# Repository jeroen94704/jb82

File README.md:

# JB82: A compact, 82-key mechanical keyboard

I'm a bit of a keyboard nerd, and my life's problem was that I couldn't find a keyboard that perfectly fit my preferences:

* Reasonably compact
* Full row of dedicated F-keys
* A complete set of nav-keys (home/end, ins/del, pgup/pgdn)
* Not have all the keys crammed together, so I can feel my way to the nav-keys

The layout in this repo has all that. Here you will find the kicad project for the PCB design and some supporting files for the 3D-printable case (which can be found here: https://www.printables.com/model/626812-jb82-keyboard-enclosure) and the keyboard firmware.

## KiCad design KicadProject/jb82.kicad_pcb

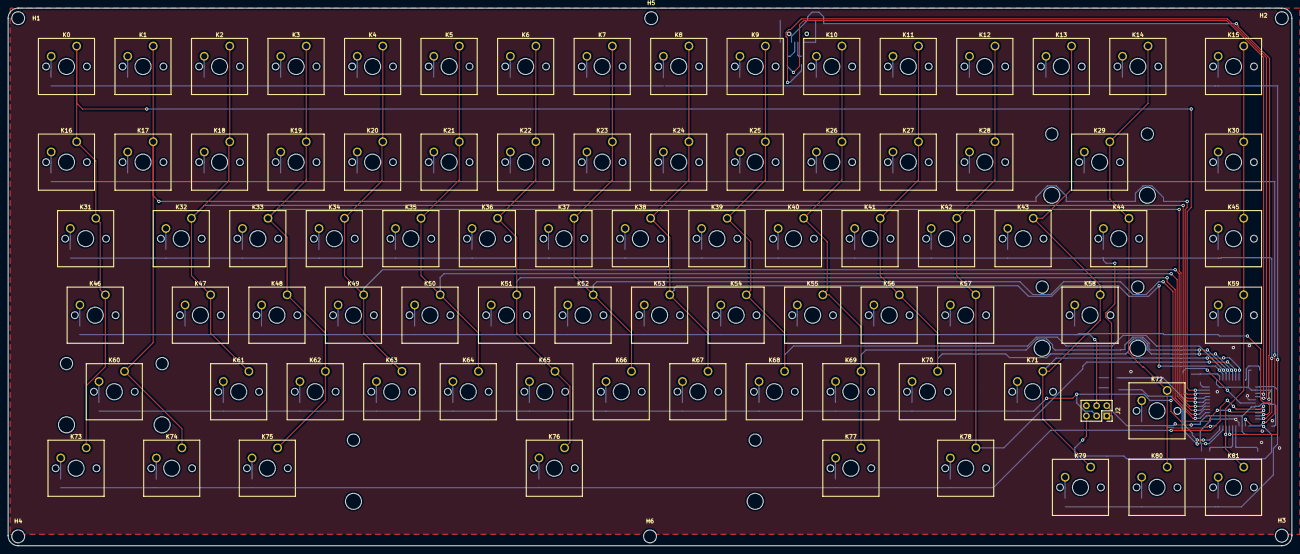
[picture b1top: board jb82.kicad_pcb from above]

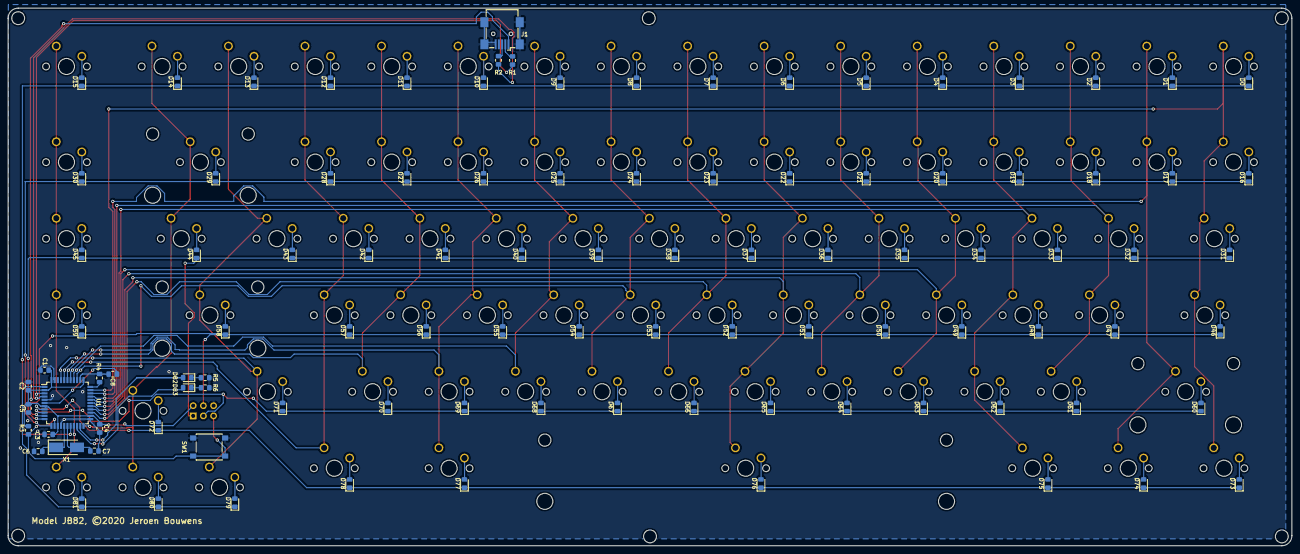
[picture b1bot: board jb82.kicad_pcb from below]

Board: 2 copper layers, 319.6 x 133.8 mm, 191 parts (102 on the bottom side), 120 nets.

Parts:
C1, C2, C3, C4: 0.1u; C_0805_2012Metric_Pad1.15x1.40mm_HandSolder
C5: 4.7u; C_0805_2012Metric_Pad1.15x1.40mm_HandSolder
C6, C7: 22p; C_0805_2012Metric_Pad1.15x1.40mm_HandSolder
C8: 1u; C_0805_2012Metric_Pad1.15x1.40mm_HandSolder
D0, D1, D2, D3, D4, D5, D6, D7, D8, D9, D10, D11, D12, D13, D14, D15, D16, D17, D18, D19, D20, D21, D22, D23, D24, D25, D26, D27, D28, D29, D30, D31, D32, D33, D34, D35, D36, D37, D38, D39, D40, D41, D42, D43, D44, D45, D46, D47, D48, D49, D50, D51, D52, D53, D54, D55, D56, D57, D58, D59, D60, D61, D62, D63, D64, D65, D66, D67, D68, D69, D70, D71, D72, D73, D74, D75, D76, D77, D78, D79, D80, D81: D; D_0805_2012Metric_Pad1.15x1.40mm_HandSolder
D82, D83: LED; LED_0805_2012Metric_Pad1.15x1.40mm_HandSolder
H1, H2, H3, H4, H5, H6: MountingHole; MountingHole_3.2mm_M3_DIN965
J1: USB_mini_micro_B; USB_Mini-B_Wuerth_65100516121_Horizontal
J2: Conn_02x03_Odd_Even; PinSocket_2x03_P2.54mm_Vertical
K0, K1, K2, K3, K4, K5, K6, K7, K8, K9, K10, K11, K12, K13, K14, K15, K16, K17, K18, K19, K20, K21, K22, K23, K24, K25, K26, K27, K28, K30, K32, K33, K34, K35, K36, K37, K38, K39, K40, K41, K42, K43, K45, K47, K48, K49, K50, K51, K52, K53, K54, K55, K56, K57, K59, K61, K62, K63, K64, K65, K66, K67, K68, K69, K70, K72, K79, K80, K81: KEYSW; SW_Cherry_MX_1.00u_PCB
K29: KEYSW; SW_Cherry_MX_2.00u_PCB
K31, K44, K77, K78: KEYSW; SW_Cherry_MX_1.50u_PCB
K46, K71: KEYSW; SW_Cherry_MX_1.75u_PCB
K58, K60: KEYSW; SW_Cherry_MX_2.25u_PCB
K73, K74, K75: KEYSW; SW_Cherry_MX_1.25u_PCB
K76: KEYSW; SW_Cherry_MX_6.25u_PCB
R1, R2: 22; R_0805_2012Metric_Pad1.15x1.40mm_HandSolder
R3, R4: 10k; R_0805_2012Metric_Pad1.15x1.40mm_HandSolder
R5, R6: 180R; R_0805_2012Metric_Pad1.15x1.40mm_HandSolder
SW1: SW_PUSH; SW_Push_1P1T_NO_6x6mm_H9.5mm
U1: ATMEGA32U4; TQFP-44_10x10mm_P0.8mm
X1: XTAL; Crystal_SMD_5032-2Pin_5.0x3.2mm_HandSoldering

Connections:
/Col_0: K0.1, K16.1, K31.1, K46.1, K73.1, U1.32
/Col_1: K1.1, K17.1, K60.1, K74.1, U1.31
/Col_2: K2.1, K18.1, K32.1, K47.1, K61.1, U1.30
/Col_3: K3.1, K19.1, K33.1, K48.1, K62.1, K75.1, U1.29
/Col_4: K4.1, K20.1, K34.1, K49.1, K63.1, U1.28
/Col_5: K5.1, K21.1, K35.1, K50.1, K64.1, U1.27
/Col_6: K6.1, K22.1, K36.1, K51.1, K65.1, K76.1, U1.26
/Col_7: K7.1, K23.1, K37.1, K52.1, K66.1, U1.25
/Col_8: K8.1, K24.1, K38.1, K53.1, K67.1, U1.36
/Col_9: K9.1, K25.1, K39.1, K54.1, K68.1, U1.37
/Col_10: K10.1, K26.1, K40.1, K55.1, K69.1, K77.1, U1.38
/Col_11: K11.1, K27.1, K41.1, K56.1, K70.1, U1.39
/Col_12: K12.1, K28.1, K42.1, K57.1, K78.1, U1.40
/Col_13: K13.1, K43.1, K58.1, K71.1, K79.1, U1.41
/Col_14: K14.1, K29.1, K44.1, K72.1, K80.1, U1.22
/Col_15: K15.1, K30.1, K45.1, K59.1, K81.1, U1.19
/Misc1: D82.2, U1.21
/Misc2: D83.2, U1.20
/Reset: J2.5, R3.1, SW1.2, U1.13
/Row_0: D0.1, D1.1, D2.1, D3.1, D4.1, D5.1, D6.1, D7.1, D8.1, D9.1, D10.1, D11.1, D12.1, D13.1, D14.1, D15.1, U1.18
/Row_1: D16.1, D17.1, D18.1, D19.1, D20.1, D21.1, D22.1, D23.1, D24.1, D25.1, D26.1, D27.1, D28.1, D29.1, D30.1, U1.12
/Row_2: D31.1, D32.1, D33.1, D34.1, D35.1, D36.1, D37.1, D38.1, D39.1, D40.1, D41.1, D42.1, D43.1, D44.1, D45.1, J2.1, U1.11
/Row_3: D46.1, D47.1, D48.1, D49.1, D50.1, D51.1, D52.1, D53.1, D54.1, D55.1, D56.1, D57.1, D58.1, D59.1, J2.4, U1.10
/Row_4: D60.1, D61.1, D62.1, D63.1, D64.1, D65.1, D66.1, D67.1, D68.1, D69.1, D70.1, D71.1, J2.3, U1.9
/Row_5: D72.1, D73.1, D74.1, D75.1, D76.1, D77.1, D78.1, U1.8
/Row_6: D79.1, D80.1, D81.1, U1.1
GND: C1.2, C2.2, C3.2, C4.2, C5.2, C6.2, C7.2, C8.2, J1.5, J1.6, J2.6, R4.1, R5.2, R6.2, SW1.1, U1.5, U1.15, U1.23, U1.35, U1.43
unnamed: C6.1, U1.16, X1.1
unnamed: C7.1, U1.17, X1.2
unnamed: C8.1, U1.6
unnamed: D0.2, K0.2
unnamed: D1.2, K1.2
unnamed: D2.2, K2.2
unnamed: D3.2, K3.2
unnamed: D4.2, K4.2
unnamed: D5.2, K5.2
unnamed: D6.2, K6.2
unnamed: D7.2, K7.2
unnamed: D8.2, K8.2
unnamed: D9.2, K9.2
unnamed: D10.2, K10.2
unnamed: D11.2, K11.2
unnamed: D12.2, K12.2
unnamed: D13.2, K13.2
unnamed: D14.2, K14.2
unnamed: D15.2, K15.2
unnamed: D16.2, K16.2
unnamed: D17.2, K17.2
unnamed: D18.2, K18.2
unnamed: D19.2, K19.2
unnamed: D20.2, K20.2
unnamed: D21.2, K21.2
unnamed: D22.2, K22.2
unnamed: D23.2, K23.2
unnamed: D24.2, K24.2
unnamed: D25.2, K25.2
unnamed: D26.2, K26.2
unnamed: D27.2, K27.2
unnamed: D28.2, K28.2
unnamed: D29.2, K29.2
unnamed: D30.2, K30.2
unnamed: D31.2, K31.2
unnamed: D32.2, K32.2
unnamed: D33.2, K33.2
unnamed: D34.2, K34.2
unnamed: D35.2, K35.2
unnamed: D36.2, K36.2
unnamed: D37.2, K37.2
unnamed: D38.2, K38.2
unnamed: D39.2, K39.2
unnamed: D40.2, K40.2
unnamed: D41.2, K41.2
unnamed: D42.2, K42.2
unnamed: D43.2, K43.2
unnamed: D44.2, K44.2
unnamed: D45.2, K45.2
unnamed: D46.2, K46.2
unnamed: D47.2, K47.2
unnamed: D48.2, K48.2
unnamed: D49.2, K49.2
unnamed: D50.2, K50.2
unnamed: D51.2, K51.2
unnamed: D52.2, K52.2
unnamed: D53.2, K53.2
unnamed: D54.2, K54.2
unnamed: D55.2, K55.2
unnamed: D56.2, K56.2
unnamed: D57.2, K57.2
unnamed: D58.2, K58.2
unnamed: D59.2, K59.2
unnamed: D60.2, K60.2
unnamed: D61.2, K61.2
unnamed: D62.2, K62.2
unnamed: D63.2, K63.2
unnamed: D64.2, K64.2
unnamed: D65.2, K65.2
unnamed: D66.2, K66.2
unnamed: D67.2, K67.2
unnamed: D68.2, K68.2
unnamed: D69.2, K69.2
unnamed: D70.2, K70.2
unnamed: D71.2, K71.2
unnamed: D72.2, K72.2
unnamed: D73.2, K73.2
unnamed: D74.2, K74.2
unnamed: D75.2, K75.2
unnamed: D76.2, K76.2
unnamed: D77.2, K77.2
unnamed: D78.2, K78.2
unnamed: D79.2, K79.2
unnamed: D80.2, K80.2
unnamed: D81.2, K81.2
unnamed: D82.1, R5.1
unnamed: D83.1, R6.1
unnamed: J1.2, R1.2
unnamed: J1.3, R2.2
unnamed: R1.1, U1.3
unnamed: R2.1, U1.4
unnamed: R4.2, U1.33
VCC: C1.1, C2.1, C3.1, C4.1, C5.1, J1.1, J2.2, R3.2, U1.2, U1.7, U1.14, U1.24, U1.34, U1.44

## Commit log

2020-07-05 Added kicad project, DXFfiles from case builder, settings for the firmware builder and the raw layout from the keyboard layout editor
2020-07-05 Added some text to the README
2020-07-05 Added license

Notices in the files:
KicadProject/jb82.kicad_pcb:
Model JB82, ©2020 Jeroen Bouwens
